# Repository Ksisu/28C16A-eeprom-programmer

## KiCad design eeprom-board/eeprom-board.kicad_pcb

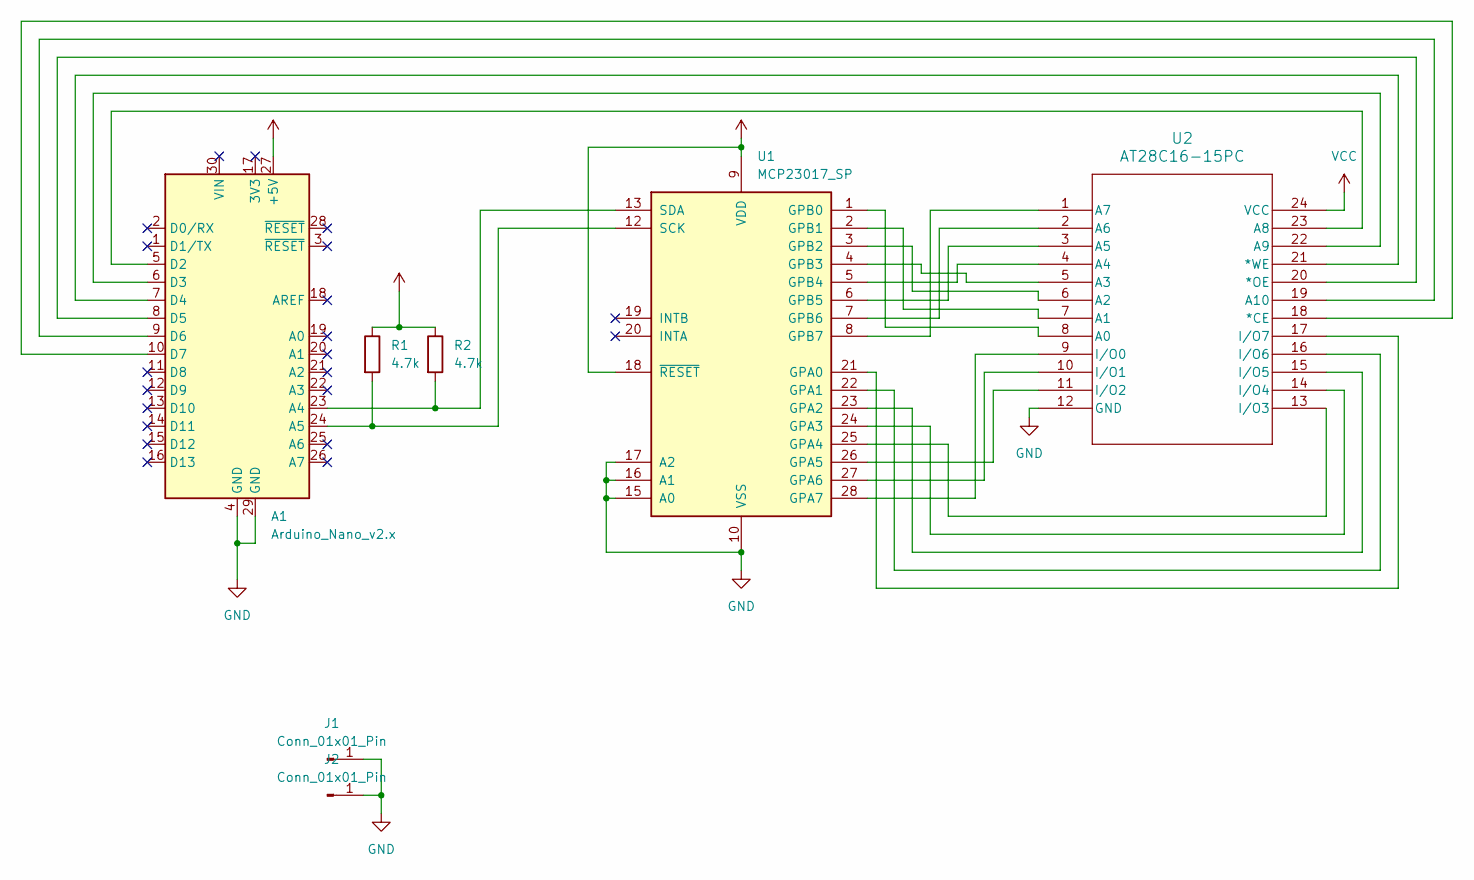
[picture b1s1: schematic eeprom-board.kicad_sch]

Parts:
A1: Arduino_Nano_v2.x; Arduino_Nano
J1, J2: Conn_01x01_Pin; PinHeader_1x01_P1.00mm_Vertical
R1, R2: 4.7k; R_Axial_DIN0207_L6.3mm_D2.5mm_P7.62mm_Horizontal
U1: MCP23017_SP; DIP-28_W7.62mm
U2: AT28C16-15PC; DIP-24_18.0mmx34.29mm_W15.24mm

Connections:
GND: A1.4 (GND), A1.29 (GND), J1.1, J2.1, U1.10 (VSS), U1.15 (A0), U1.16 (A1), U1.17 (A2), U2.12 (GND)
unnamed: A1.23 (A4), R2.2, U1.13 (SDA)
unnamed: A1.24 (A5), R1.2, U1.12 (SCK)
unnamed: A1.5 (D2), U2.23 (A8)
unnamed: A1.6 (D3), U2.22 (A9)
unnamed: A1.7 (D4), U2.21 (*WE)
unnamed: A1.8 (D5), U2.20 (*OE)
unnamed: A1.9 (D6), U2.19 (A10)
unnamed: A1.10 (D7), U2.18 (*CE)
unnamed: U1.21 (GPA0), U2.17 (I/O7)
unnamed: U1.22 (GPA1), U2.16 (I/O6)
unnamed: U1.23 (GPA2), U2.15 (I/O5)
unnamed: U1.24 (GPA3), U2.14 (I/O4)
unnamed: U1.25 (GPA4), U2.13 (I/O3)
unnamed: U1.26 (GPA5), U2.11 (I/O2)
unnamed: U1.27 (GPA6), U2.10 (I/O1)
unnamed: U1.28 (GPA7), U2.9 (I/O0)
unnamed: U1.1 (GPB0), U2.8 (A0)
unnamed: U1.2 (GPB1), U2.7 (A1)
unnamed: U1.3 (GPB2), U2.6 (A2)
unnamed: U1.4 (GPB3), U2.5 (A3)
unnamed: U1.5 (GPB4), U2.4 (A4)
unnamed: U1.6 (GPB5), U2.3 (A5)
unnamed: U1.7 (GPB6), U2.2 (A6)
unnamed: U1.8 (GPB7), U2.1 (A7)
VCC: A1.27 (+5V), R1.1, R2.1, U1.9 (VDD), U1.18 (~RESET), U2.24 (VCC)

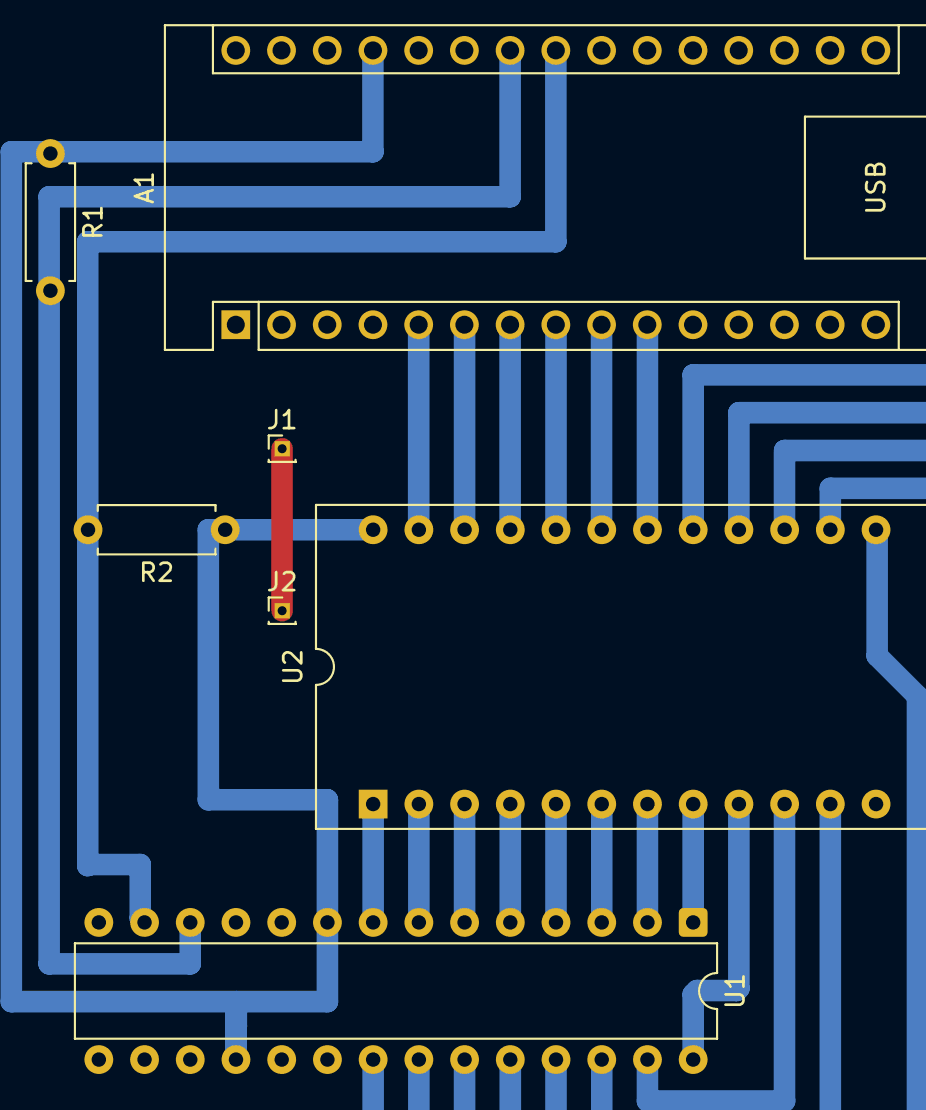
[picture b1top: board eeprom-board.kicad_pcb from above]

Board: 2 copper layers, 7 parts (0 on the bottom side), 26 nets.

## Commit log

2025-08-15 version 1.0.0
